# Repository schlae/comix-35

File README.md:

# COMIX-35 Home Computer
The COMIX-35 is an open-source clone of the 1980s COMX-35 8-bit home computer.
It uses the RCA 1802 microprocessor which is strange and slow but holds the
distinction of being the first CMOS microprocessor. The "35" is because the
original computer has 32K of main memory + 3K of video RAM.

There are a number of differences between the COMIX-35 and the original:

* Single +5V power supply
* Uses SRAM; no stolen cycles for DRAM refresh
* Configurable PAL or NTSC by changing three jumpers and swapping a crystal
* Additional CPU crystal for a new turbo mode
* Mechanical key switches for your typing comfort
* Cassette input data light indicates incoming information

## Design files

Here are the design files. The BOM includes Mouser part numbers for everything
except the CDP1802, CDP1869, CDP1870, CDP1871, the trimmer capacitor (optional),
and the expansion slot header (also optional). I recommend you purchase IC
sockets for the four CDP parts, as well as for the ROM chip U15.

[Schematic](https://github.com/schlae/comix-35/blob/master/COMIX-35.pdf)

[Bill of Materials](https://github.com/schlae/comix-35/blob/master/COMIX-35.csv)

[Fab Files](https://github.com/schlae/comix-35/blob/master/fab/COMIX-35.zip)

The board is rather large, at 12 x 6.5 inches (304.8 x 165.1 mm), but it does
include the keyboard. It is a 2-layer design so it should be relatively cheap
to manufacture. A word of advice: pick out your keycap set first, then choose
the PCB color to match it.

The keyboard keyswitches are easily substituted for lower-cost ones from other
vendors. I recommend you purchase DSA-profile keycaps since some of the keys
are located in rows that are not typical. I ended up buying the [YMDK 125 DSA Dye Sub 9009 Retro PBT Full Keyset for MX](https://www.amazon.com/gp/product/B083L6FVPN/). You can choose whatever you want, but make sure there is a 1 unit
control key and a 1.25 unit shift key. The enter key needs to be 1.5 unit, so
I just used the tab key for that instead. If you have any doubt, check the PCB
layout which has the key cap unit sizes marked below each key.

I have not included part numbers for the 0.1" headers which usually come as a
long strip that you break into the appropriately-sized sections.

Most other components may be safely substituted. U4 is a little tricky. It
should be a 74HCU04 in order for the oscillators to operate, but in a pinch,
a 74HC04 will also work. A 74LS04 or a part from another logic family will
not work.

## Assembly notes
Since the standard COMX-35 ROM configures the CDP1869 to use extra-tall
characters, you need to tie CDP1869 pin 25 to CMA3. Do this by soldering a
jumper wire from pin 1-2 on JP6. If you wish to write your own code to deal
with short characters and more text pages, then install a 0.1" header and
jumper instead.

The default configuration for PAL is as follows:

| Location | PAL     | NTSC    |
| -------- | ------- | ------- |
| JP1      | 2-3     | 1-2     |
| JP2      | 2-3     | 1-2     |
| JP3      | 2-3     | 1-2     |
| Y1       | 17.734 MHz | 14.318MHz |

The trimmer capacitor, C12, is optional. It allows you to adjust the color
image for best clarity. If you don't use it, then just stuff C13 with a 22pF
capacitor.

You can also configure your COMIX-35 for turbo mode which allows the CPU to
run at much higher frequencies than the original computer, limited only by
the maximum frequency of your particular CDP1802. Check the datasheet for the
variation you have, or experiment. Turbo mode is enabled by jumpering JP4 to
position 1-2. This enables the clock oscillator installed at Y3. To run at the
standard speed, set JP4 to 2-3.

If you use a 28C256 or 27C256 ROM, jumper JP5 will allow you to select between
the upper and lower 16K of ROM. This is useful if you want to use store two
different ROM binaries, such as the standard COMX-35 ROM and your own custom
program.

The COMX-35 ROM image is relatively easy to find so I will not provide it here.

## Video adjustments

There are two trimmer resistors that adjust the video:

* RV3 adjusts the sync pulse amplitude
* RV4 sets the overall video amplitude

The simplest way to get it working is to use an oscilloscope to set the sync
pulse amplitude to about 300mV and the video amplitude to about 700mV. If you
don't have an oscilloscope, set RV4 to the maximum, set RV3 to the minimum,
and then slowly increase RV3 until you get a stable picture. If the colors
are not saturated enough, you can decrease RV4.

The C12 trimmer capacitor, if you installed it, adjusts the frequency of the
colorburst by a small amount. Since the colorburst and the pixel clock are not
sychronized, you'll get a "shimmering" effect on colored pixels. Adjust C12
until you can't see shimmering anymore. 

## Loading programs off a computer using the cassette port
The process I've had success with is this:

* Run the [Emma 02 emulator](https://www.emma02.hobby-site.com/). Turn off SB
mode, turn off Turbo LOAD/SAVE. Make sure Auto LOAD/SAVE is turned on.
* Hit run. Press enter to go past the COMX screen and get to the BASIC prompt.
* Click the LOAD button and select the program you are interested in.
* From BASIC, type PSAVE.
* Name the file (it is actually a raw sound file, not WAV.)
* It will take a while but it will eventually save the cassette sound.
* Load the raw file in Audacity using File-\>Import-\>Raw Data. Select 22050 as
the sampling rate, mono, signed 16 bit little endian.
* You may wish to save the program as a regular WAV file at this point.
* Connect an audio cable between the COMIX-35's EAR jack and your computer's
speaker output.
* Make sure your computer has absolutely no audio processing going on at all.
No echo, no equalizer, nothing at all. You may have to really crank up the
volume.
* Hit play, and then adjust the input bias control until the data LED flickers.
* Stop, rewind, hit play, and then (on the COMIX-35) type "PLOAD" and hit
enter. If everything works, PLOAD will return you back to the BASIC prompt.
* Type RUN and hit enter to start the program.

The cassette interface is a bit tricky to work due to various reasons. The
input circuit uses a Schmitt-trigger buffer, so the DC bias of the incoming
audio signal must be adjusted to the halfway point of that threshold. This
is what the INPUT BIAS trimmer does.

You also need enough volume to be able to exceed the rising and falling
thresholds.

Tips and tricks if things don't work right the first time:
* Does your computer *really* provide clean audio? You've turned off all
effects processing? Audio managers, headphone bass boosters--all that *must* 
be turned off!
* Check your cables
* Check the volume level on the PC. If it is too low, it will not work
* Connect an oscilloscope to the cathode of D5 and make sure you see a clean
waveform

## Compatibility
Note that I have not tested the COMIX-35 with real COMX-35 accessories, such
as the expansion chassis, RAM boards, disk controllers, etc. It should work
with all these accessories except for the RAM expansion because it uses the RAS
and CAS lines. Since the COMIX-35 does not have the DRAM refresh circuit, these
signals don't exist on the expansion connector.

## License
This work is licensed under a Creative Commons Attribution-ShareAlike 4.0
International License. See [https://creativecommons.org/licenses/by-sa/4.0/](https://creativecommons.org/licenses/by-sa/4.0/).

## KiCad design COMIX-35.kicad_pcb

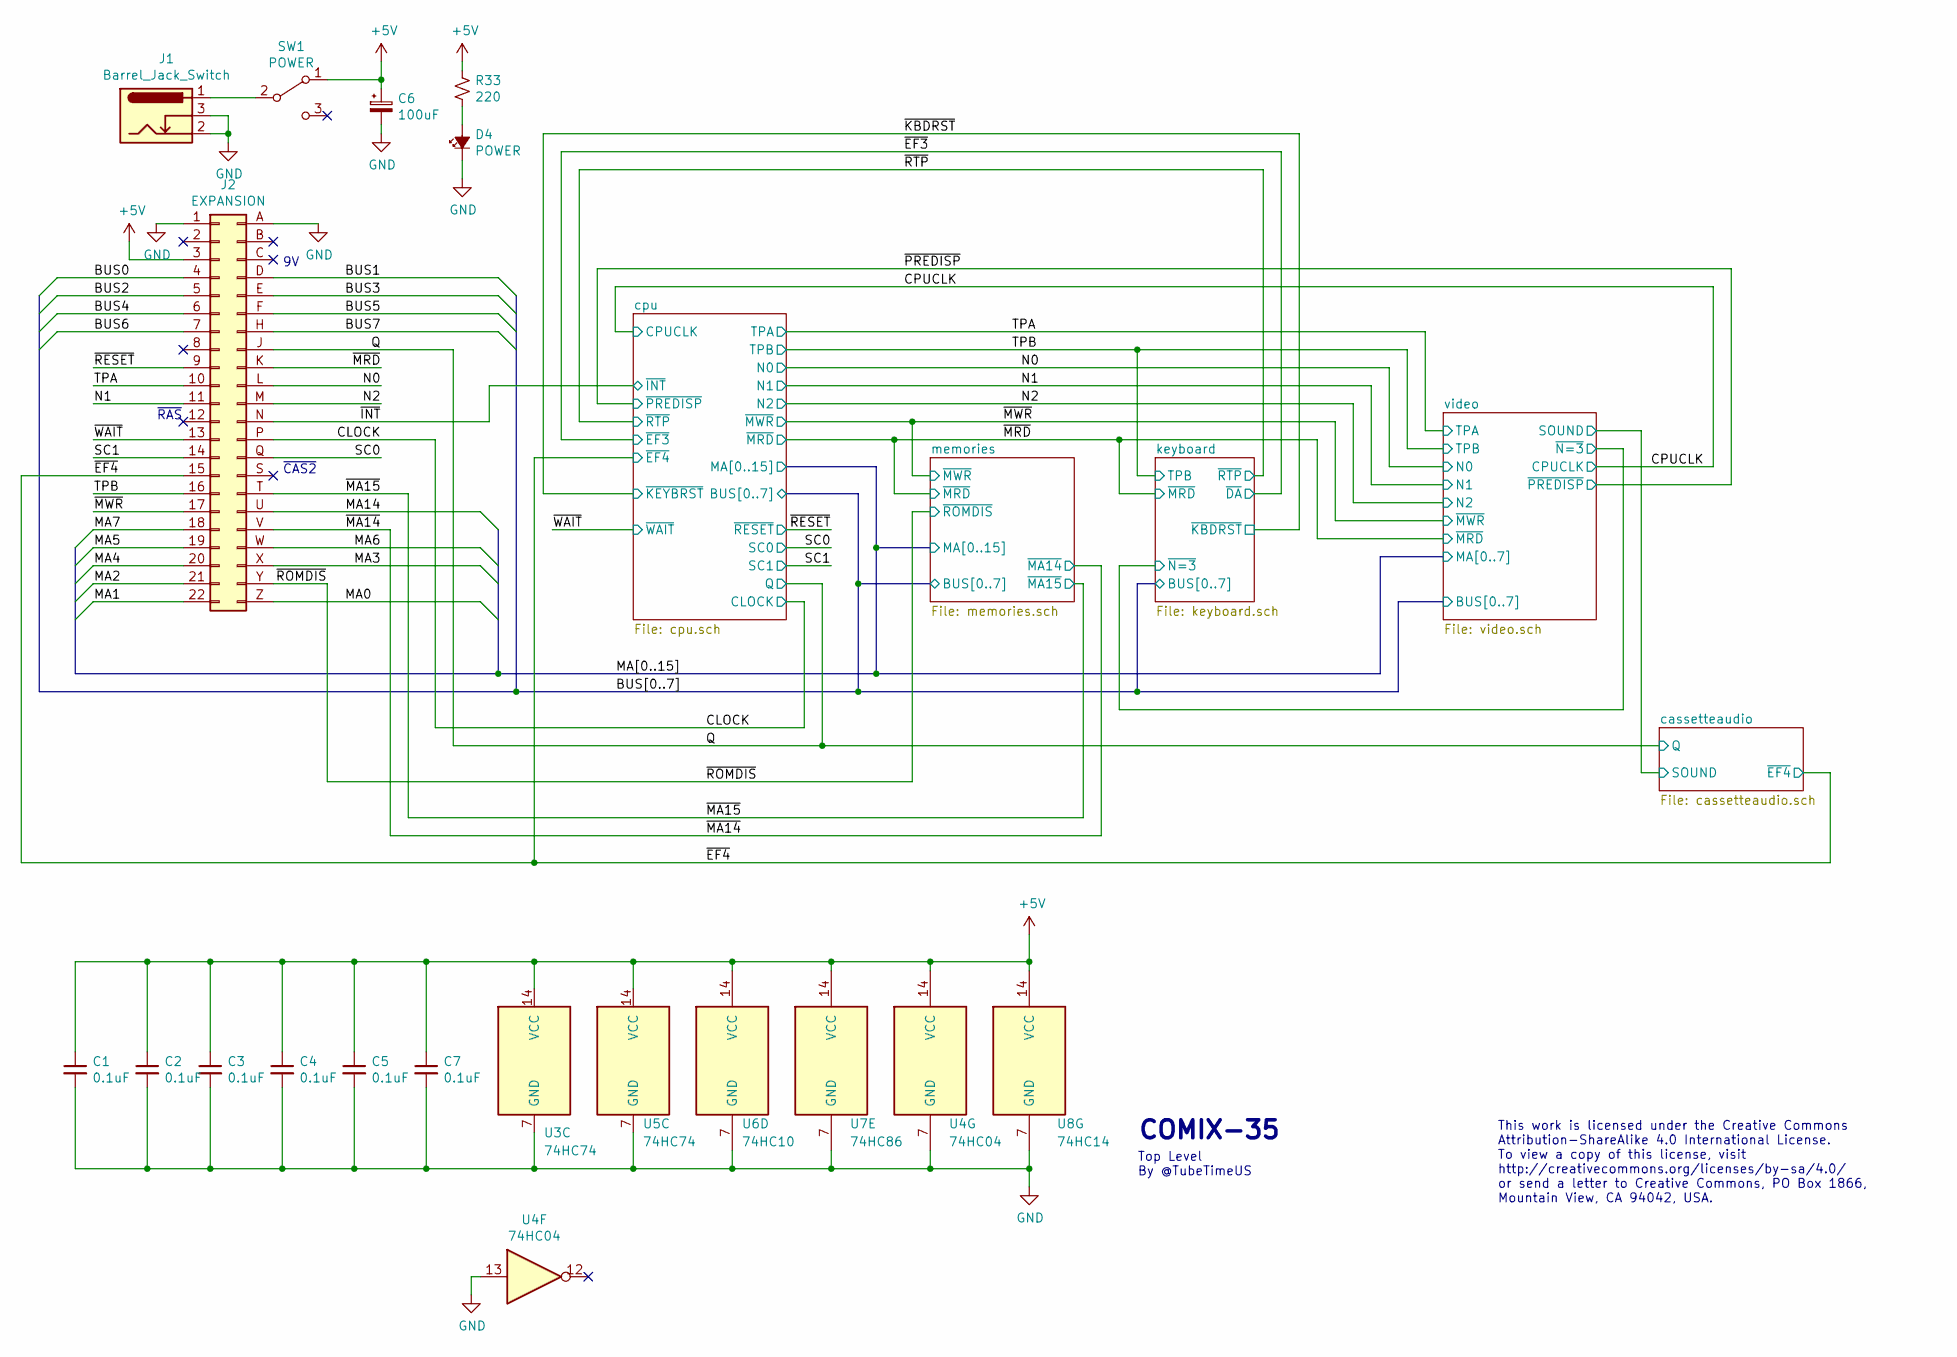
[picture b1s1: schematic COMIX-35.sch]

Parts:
C1, C2, C3, C4, C5, C7: 0.1uF; CAPAC200; Mouser 581-SA105E104M
C6: 100uF; CAPAE200P500X1100; Mouser 667-ECA-1CM101I
D4: POWER; LED_D5.0mm; Mouser 859-LTL-4213
J1: Barrel_Jack_Switch; CUI_PJ-002B; Mouser 490-PJ-002B
J2: EXPANSION; SULLINS_EBC22DRAS_ALT; Digikey S3316-ND
R33: 220; RESA500; Mouser 603-CFR-25JR-52220R
SW1: POWER; NKK_CS12ANW03; Mouser 633-CS12ANW03
U3, U5: 74HC74; DIP254P762X635-14; Mouser 595-SN74HC74N
U4: 74HC04; DIP254P762X635-14; Mouser 595-SN74HC04N
U6: 74HC10; DIP254P762X635-14; Mouser 595-SN74HC10N
U7: 74HC86; DIP254P762X635-14; Mouser 595-SN74HC86N
U8: 74HC14; DIP254P762X635-14; Mouser 595-SN74HC14N

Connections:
+5V: C1.1, C2.1, C3.1, C4.1, C5.1, C6.1, C7.1, J2.3, R33.2, SW1.1 (A), U3.14 (VCC), U4.14 (VCC), U5.14 (VCC), U6.14 (VCC), U7.14 (VCC), U8.14 (VCC); also elsewhere on the board
/BUS0: J2.4; also elsewhere on the board
/BUS1: J2.D; also elsewhere on the board
/BUS2: J2.5; also elsewhere on the board
/BUS3: J2.E; also elsewhere on the board
/BUS4: J2.6; also elsewhere on the board
/BUS5: J2.F; also elsewhere on the board
/BUS6: J2.7; also elsewhere on the board
/BUS7: J2.H; also elsewhere on the board
/CLOCK: J2.P; also elsewhere on the board
/MA0: J2.Z; also elsewhere on the board
/MA1: J2.22; also elsewhere on the board
/MA2: J2.21; also elsewhere on the board
/MA3: J2.X; also elsewhere on the board
/MA4: J2.20; also elsewhere on the board
/MA5: J2.19; also elsewhere on the board
/MA6: J2.W; also elsewhere on the board
/MA7: J2.18; also elsewhere on the board
/MA14: J2.U; also elsewhere on the board
/N0: J2.L; also elsewhere on the board
/N1: J2.11; also elsewhere on the board
/N2: J2.M; also elsewhere on the board
/Q: J2.J; also elsewhere on the board
/SC0: J2.Q; also elsewhere on the board
/SC1: J2.14; also elsewhere on the board
/TPA: J2.10; also elsewhere on the board
/TPB: J2.16; also elsewhere on the board
/~EF4: J2.15; also elsewhere on the board
/~INT: J2.N; also elsewhere on the board
/~MA14: J2.V; also elsewhere on the board
/~MA15: J2.T; also elsewhere on the board
/~MRD: J2.K; also elsewhere on the board
/~MWR: J2.17; also elsewhere on the board
/~RESET: J2.9; also elsewhere on the board
/~ROMDIS: J2.Y; also elsewhere on the board
/~WAIT: J2.13; also elsewhere on the board
GND: C1.2, C2.2, C3.2, C4.2, C5.2, C6.2, C7.2, D4.1 (K), J1.2, J1.3, J2.1, J2.A, U3.7 (GND), U4.7 (GND), U4.13, U5.7 (GND), U6.7 (GND), U7.7 (GND), U8.7 (GND); also elsewhere on the board
unnamed: D4.2 (A), R33.1
unnamed: J1.1, SW1.2 (B)

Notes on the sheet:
~RAS
~CAS2
This work is licensed under the Creative Commons Attribution-ShareAlike 4.0 International License. To view a copy of this license, visit http://creativecommons.org/licenses/by-sa/4.0/ or send a letter to Creative Commons, PO Box 1866, Mountain View, CA 94042, USA.
COMIX-35
Top Level By @TubeTimeUS

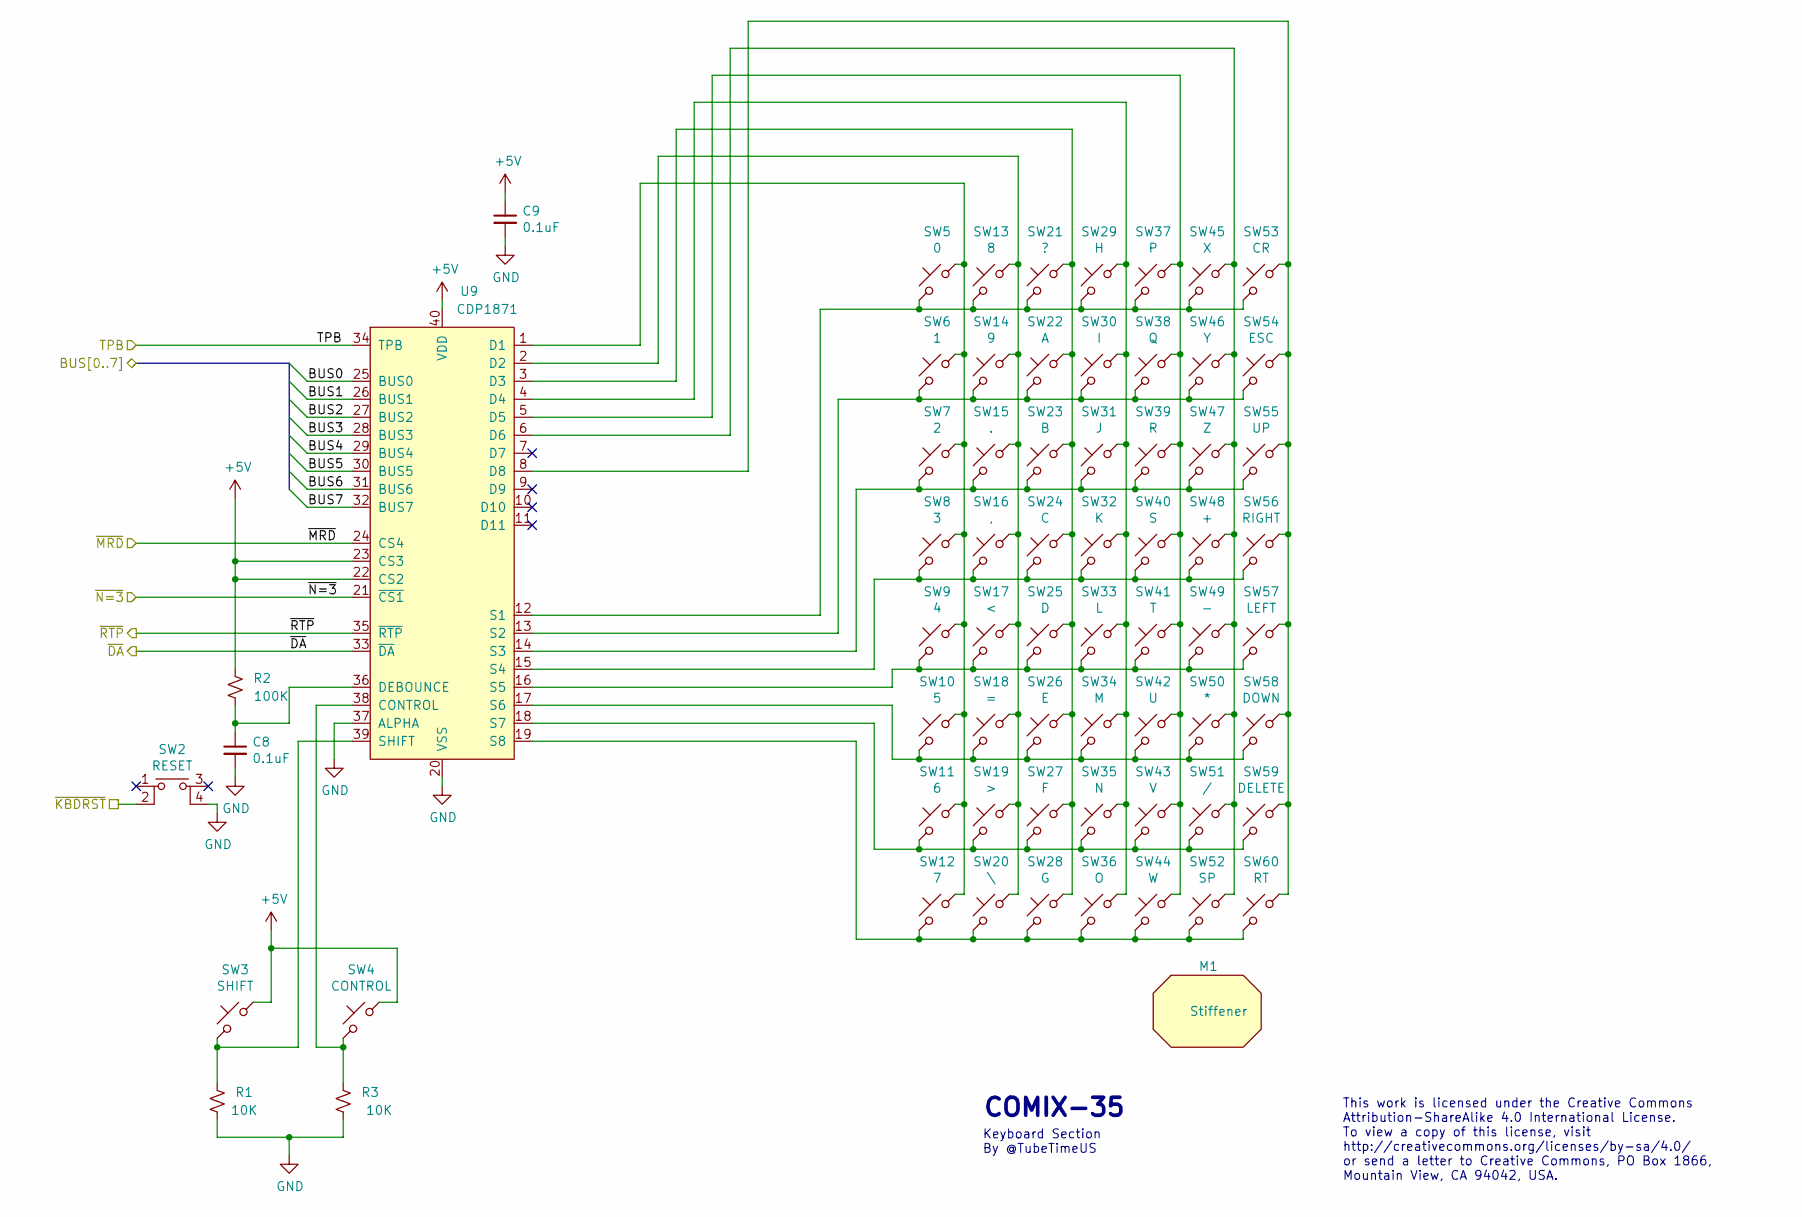
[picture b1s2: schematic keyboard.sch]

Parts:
C8, C9: 0.1uF; CAPAC200; Mouser 581-SA105E104M
M1: Stiffener; CHERRY_ST2; Mouser 540-0G990743
R1, R3: 10K; RESA500; Mouser 603-CFR-25JB-52-10K
R2: 100K; RESA500; Mouser 603-CFR-25JB-52-100K
SW2: RESET; ESWITCH_TL1105; Mouser 612-TL1105B
SW3: SHIFT; CHERRY_MX_125; Mouser 540-MX1A-11NW
SW4: CONTROL; CHERRY_MX; Mouser 540-MX1A-11NW
SW5: 0; CHERRY_MX; Mouser 540-MX1A-11NW
SW6: 1; CHERRY_MX; Mouser 540-MX1A-11NW
SW7: 2; CHERRY_MX; Mouser 540-MX1A-11NW
SW8: 3; CHERRY_MX; Mouser 540-MX1A-11NW
SW9: 4; CHERRY_MX; Mouser 540-MX1A-11NW
SW10: 5; CHERRY_MX; Mouser 540-MX1A-11NW
SW11: 6; CHERRY_MX; Mouser 540-MX1A-11NW
SW12: 7; CHERRY_MX; Mouser 540-MX1A-11NW
SW13: 8; CHERRY_MX; Mouser 540-MX1A-11NW
SW14: 9; CHERRY_MX; Mouser 540-MX1A-11NW
SW15: .; CHERRY_MX; Mouser 540-MX1A-11NW
SW16: ,; CHERRY_MX; Mouser 540-MX1A-11NW
SW17: <; CHERRY_MX; Mouser 540-MX1A-11NW
SW18: =; CHERRY_MX; Mouser 540-MX1A-11NW
SW19: >; CHERRY_MX; Mouser 540-MX1A-11NW
SW20: \\; CHERRY_MX; Mouser 540-MX1A-11NW
SW21: ?; CHERRY_MX; Mouser 540-MX1A-11NW
SW22: A; CHERRY_MX; Mouser 540-MX1A-11NW
SW23: B; CHERRY_MX; Mouser 540-MX1A-11NW
SW24: C; CHERRY_MX; Mouser 540-MX1A-11NW
SW25: D; CHERRY_MX; Mouser 540-MX1A-11NW
SW26: E; CHERRY_MX; Mouser 540-MX1A-11NW
SW27: F; CHERRY_MX; Mouser 540-MX1A-11NW
SW28: G; CHERRY_MX; Mouser 540-MX1A-11NW
SW29: H; CHERRY_MX; Mouser 540-MX1A-11NW
SW30: I; CHERRY_MX; Mouser 540-MX1A-11NW
SW31: J; CHERRY_MX; Mouser 540-MX1A-11NW
SW32: K; CHERRY_MX; Mouser 540-MX1A-11NW
SW33: L; CHERRY_MX; Mouser 540-MX1A-11NW
SW34: M; CHERRY_MX; Mouser 540-MX1A-11NW
SW35: N; CHERRY_MX; Mouser 540-MX1A-11NW
SW36: O; CHERRY_MX; Mouser 540-MX1A-11NW
SW37: P; CHERRY_MX; Mouser 540-MX1A-11NW
SW38: Q; CHERRY_MX; Mouser 540-MX1A-11NW
SW39: R; CHERRY_MX; Mouser 540-MX1A-11NW
SW40: S; CHERRY_MX; Mouser 540-MX1A-11NW
SW41: T; CHERRY_MX; Mouser 540-MX1A-11NW
SW42: U; CHERRY_MX; Mouser 540-MX1A-11NW
SW43: V; CHERRY_MX; Mouser 540-MX1A-11NW
SW44: W; CHERRY_MX; Mouser 540-MX1A-11NW
SW45: X; CHERRY_MX; Mouser 540-MX1A-11NW
SW46: Y; CHERRY_MX; Mouser 540-MX1A-11NW
SW47: Z; CHERRY_MX; Mouser 540-MX1A-11NW
SW48: +; CHERRY_MX; Mouser 540-MX1A-11NW
SW49: -; CHERRY_MX; Mouser 540-MX1A-11NW
SW50: *; CHERRY_MX; Mouser 540-MX1A-11NW
SW51: /; CHERRY_MX; Mouser 540-MX1A-11NW
SW52: SP; CHERRY_MX_625; Mouser 540-MX1A-11NW
SW53: CR; CHERRY_MX_150; Mouser 540-MX1A-11NW
SW54: ESC; CHERRY_MX; Mouser 540-MX1A-11NW
SW55: UP; CHERRY_MX; Mouser 540-MX1A-11NW
SW56: RIGHT; CHERRY_MX; Mouser 540-MX1A-11NW
SW57: LEFT; CHERRY_MX; Mouser 540-MX1A-11NW
SW58: DOWN; CHERRY_MX; Mouser 540-MX1A-11NW
SW59: DELETE; CHERRY_MX; Mouser 540-MX1A-11NW
SW60: RT; CHERRY_MX; Mouser 540-MX1A-11NW
U9: CDP1871; DIP254P1524X635-40

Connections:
+5V: C9.1, R2.1, SW3.1, SW4.1, U9.22 (CS2), U9.23 (CS3), U9.40 (VDD); also elsewhere on the board
/BUS0: U9.25 (BUS0); also elsewhere on the board
/BUS1: U9.26 (BUS1); also elsewhere on the board
/BUS2: U9.27 (BUS2); also elsewhere on the board
/BUS3: U9.28 (BUS3); also elsewhere on the board
/BUS4: U9.29 (BUS4); also elsewhere on the board
/BUS5: U9.30 (BUS5); also elsewhere on the board
/BUS6: U9.31 (BUS6); also elsewhere on the board
/BUS7: U9.32 (BUS7); also elsewhere on the board
/TPB: U9.34 (TPB); also elsewhere on the board
/keyboard/~N=3: U9.21 (~CS1); also elsewhere on the board
/~EF3: U9.33 (~DA); also elsewhere on the board
/~KBDRST: SW2.2; also elsewhere on the board
/~MRD: U9.24 (CS4); also elsewhere on the board
/~RTP: U9.35 (~RTP); also elsewhere on the board
GND: C8.2, C9.2, R1.2, R3.2, SW2.4, U9.20 (VSS), U9.37 (ALPHA); also elsewhere on the board
unnamed: C8.1, R2.2, U9.36 (DEBOUNCE)
unnamed: R1.1, SW3.2, U9.39 (SHIFT)
unnamed: R3.1, SW4.2, U9.38 (CONTROL)
unnamed: SW5.1, SW6.1, SW7.1, SW8.1, SW9.1, SW10.1, SW11.1, SW12.1, U9.1 (D1)
unnamed: SW10.2, SW18.2, SW26.2, SW34.2, SW42.2, SW50.2, SW58.2, U9.17 (S6)
unnamed: SW11.2, SW19.2, SW27.2, SW35.2, SW43.2, SW51.2, SW59.2, U9.18 (S7)
unnamed: SW12.2, SW20.2, SW28.2, SW36.2, SW44.2, SW52.2, SW60.2, U9.19 (S8)
unnamed: SW13.1, SW14.1, SW15.1, SW16.1, SW17.1, SW18.1, SW19.1, SW20.1, U9.2 (D2)
unnamed: SW5.2, SW13.2, SW21.2, SW29.2, SW37.2, SW45.2, SW53.2, U9.12 (S1)
unnamed: SW6.2, SW14.2, SW22.2, SW30.2, SW38.2, SW46.2, SW54.2, U9.13 (S2)
unnamed: SW7.2, SW15.2, SW23.2, SW31.2, SW39.2, SW47.2, SW55.2, U9.14 (S3)
unnamed: SW8.2, SW16.2, SW24.2, SW32.2, SW40.2, SW48.2, SW56.2, U9.15 (S4)
unnamed: SW9.2, SW17.2, SW25.2, SW33.2, SW41.2, SW49.2, SW57.2, U9.16 (S5)
unnamed: SW21.1, SW22.1, SW23.1, SW24.1, SW25.1, SW26.1, SW27.1, SW28.1, U9.3 (D3)
unnamed: SW29.1, SW30.1, SW31.1, SW32.1, SW33.1, SW34.1, SW35.1, SW36.1, U9.4 (D4)
unnamed: SW37.1, SW38.1, SW39.1, SW40.1, SW41.1, SW42.1, SW43.1, SW44.1, U9.5 (D5)
unnamed: SW45.1, SW46.1, SW47.1, SW48.1, SW49.1, SW50.1, SW51.1, SW52.1, U9.6 (D6)
unnamed: SW53.1, SW54.1, SW55.1, SW56.1, SW57.1, SW58.1, SW59.1, SW60.1, U9.8 (D8)

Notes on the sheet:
This work is licensed under the Creative Commons Attribution-ShareAlike 4.0 International License. To view a copy of this license, visit http://creativecommons.org/licenses/by-sa/4.0/ or send a letter to Creative Commons, PO Box 1866, Mountain View, CA 94042, USA.
COMIX-35
Keyboard Section By @TubeTimeUS

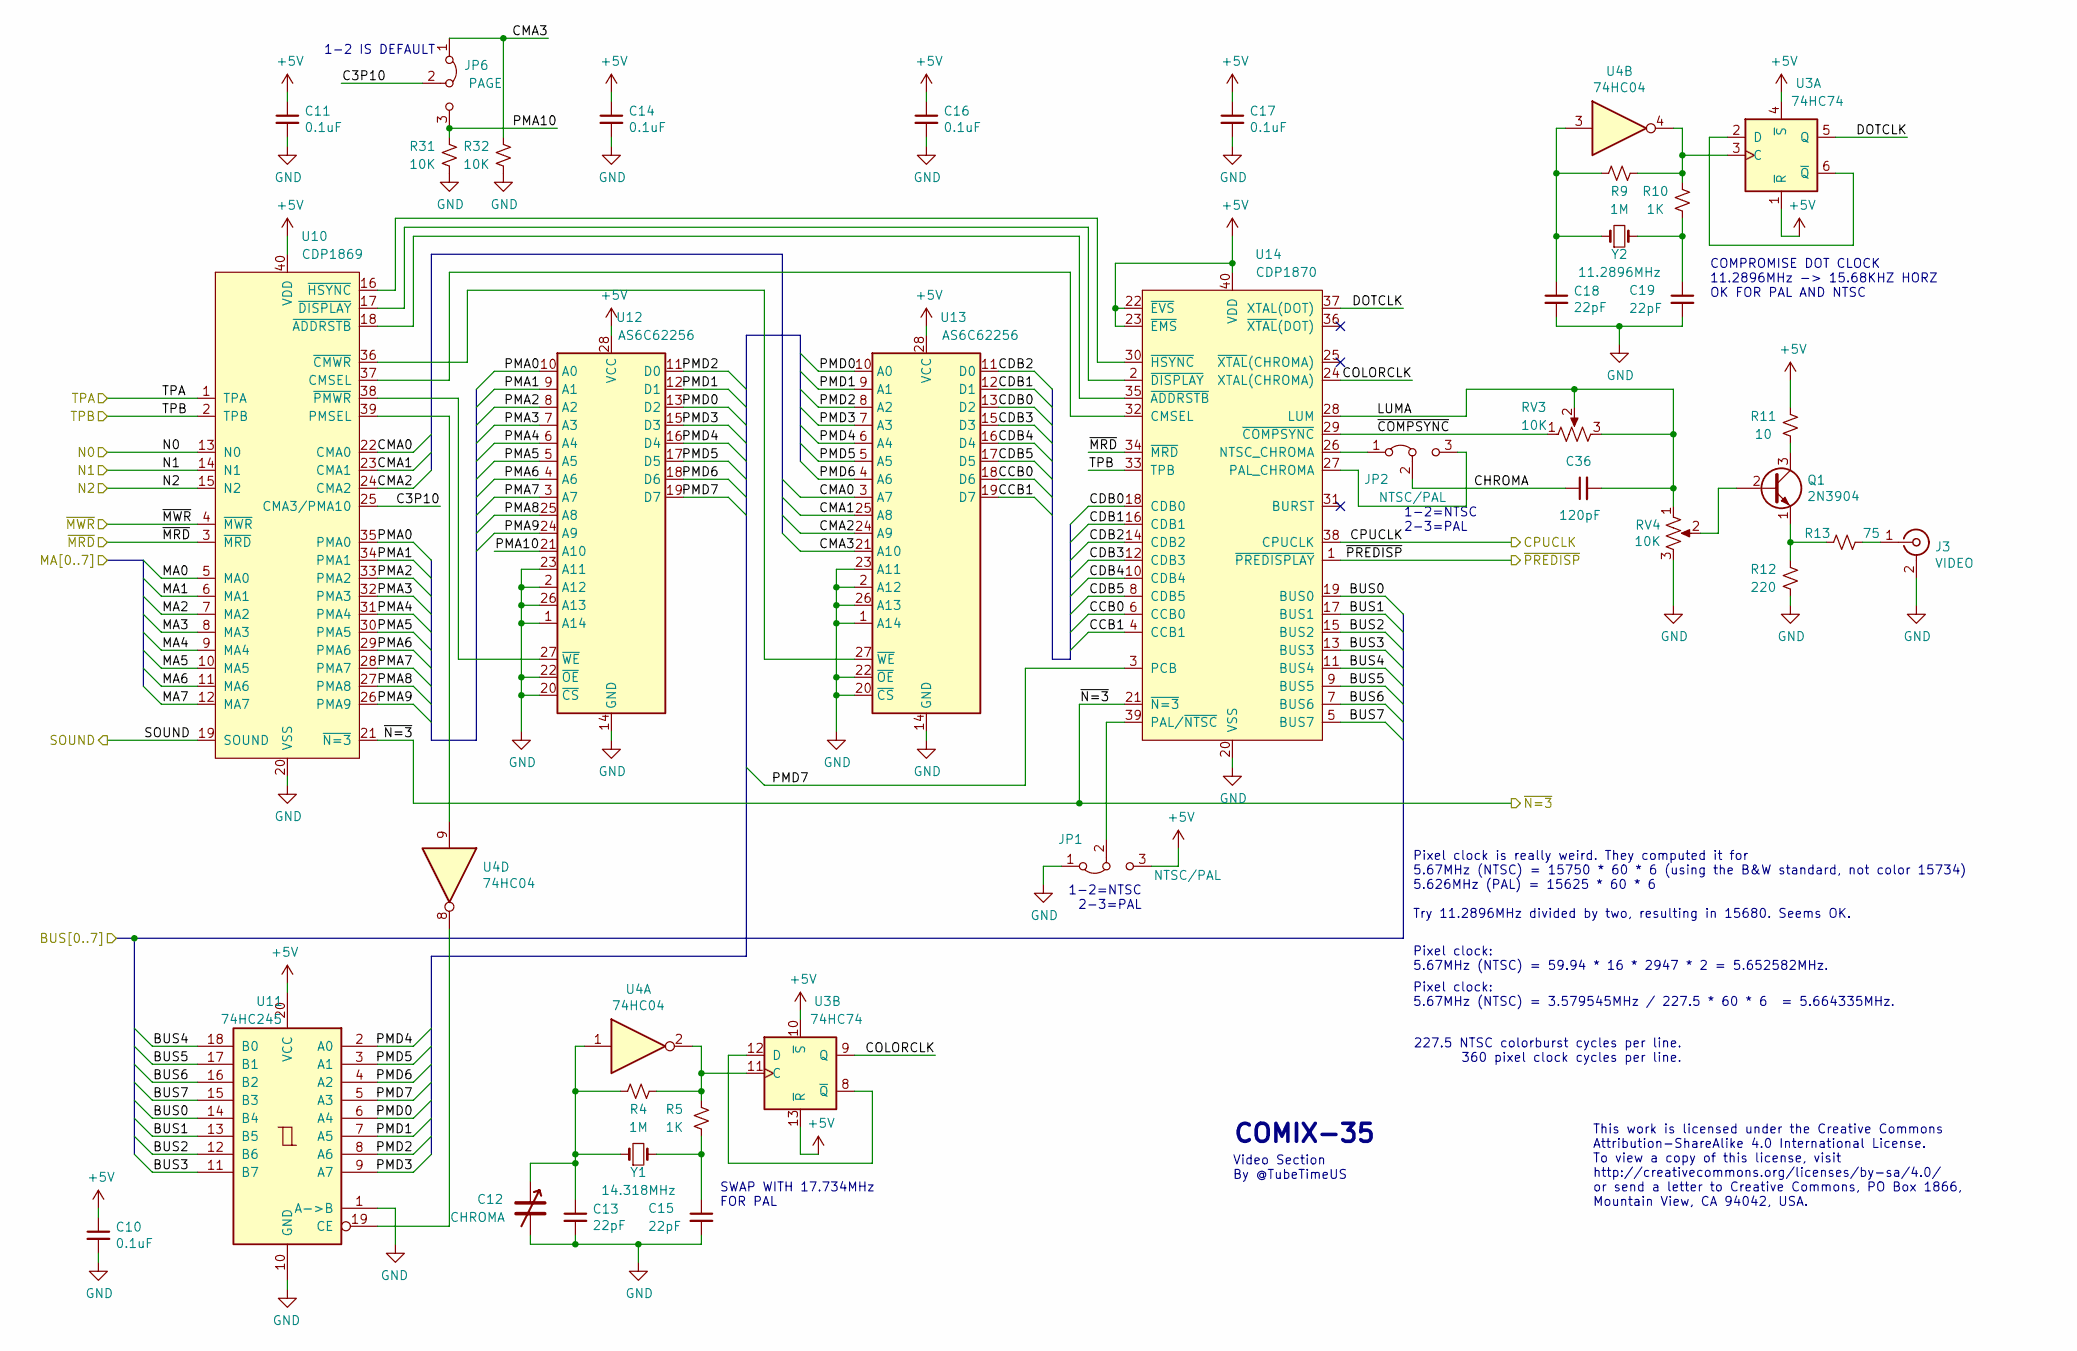
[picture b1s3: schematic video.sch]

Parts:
C10, C11, C14, C16, C17: 0.1uF; CAPAC200; Mouser 581-SA105E104M
C12: CHROMA; EW_GKG; Digikey 2447-GKG30015-ND
C13, C15, C18, C19: 22pF; CAPAC200; Mouser 810-FG28C0G2A220JNT0
C36: 120pF; CAPAC200; Mouser 810-FG28C0G1H121JNT6
J3: VIDEO; KOBICONN_161-03X0-E; Mouser 161-0360-E
JP1, JP2: NTSC/PAL; Pin_Header_Straight_1x03_Pitch2.54mm
JP6: PAGE; Pin_Header_Straight_1x03_Pitch2.54mm
Q1: 2N3904; TO92-IL; Mouser 512-2N3904BU
R4, R9: 1M; RESA500; Mouser 603-CFR-25JR-521M
R5, R10: 1K; RESA500; Mouser 603-CFR-25JR-521K
R11: 10; RESA500; Mouser 603-CFR-25JR-5210R
R12: 220; RESA500; Mouser 603-CFR-25JR-52220R
R13: 75; RESA500; Mouser 603-CFR-25JR-5275R
R31, R32: 10K; RESA500; Mouser 603-CFR-25JB-52-10K
RV3, RV4: 10K; PIHER_PT10_H01; Mouser 531-PT10H-10K-S
U3: 74HC74; DIP254P762X635-14; Mouser 595-SN74HC74N
U4: 74HC04; DIP254P762X635-14; Mouser 595-SN74HC04N
U10: CDP1869; DIP254P1524X635-40
U11: 74HC245; DIP254P762X635-20; Mouser 595-SN74HC245N
U12, U13: AS6C62256; DIP254P1524X635-28; Mouser 913-AS6C62256-55PCN
U14: CDP1870; DIP254P1524X635-40
Y1: 14.318MHz; Crystal_HC49-4H_Vertical; Mouser 815-ABL-14.31818B2
Y2: 11.2896MHz; Crystal_HC49-4H_Vertical; Mouser 815-ABL-11.2896-B4Y

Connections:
+5V: C10.1, C11.1, C14.1, C16.1, C17.1, JP1.3 (B), R11.1, U3.1 (~R), U3.4 (~S), U3.10 (~S), U3.13 (~R), U10.40 (VDD), U11.20 (VCC), U12.28 (VCC), U13.28 (VCC), U14.22 (~EVS), U14.23 (~EMS), U14.40 (VDD); also elsewhere on the board
/BUS0: U11.14 (B4), U14.19 (BUS0); also elsewhere on the board
/BUS1: U11.13 (B5), U14.17 (BUS1); also elsewhere on the board
/BUS2: U11.12 (B6), U14.15 (BUS2); also elsewhere on the board
/BUS3: U11.11 (B7), U14.13 (BUS3); also elsewhere on the board
/BUS4: U11.18 (B0), U14.11 (BUS4); also elsewhere on the board
/BUS5: U11.17 (B1), U14.9 (BUS5); also elsewhere on the board
/BUS6: U11.16 (B2), U14.7 (BUS6); also elsewhere on the board
/BUS7: U11.15 (B3), U14.5 (BUS7); also elsewhere on the board
/CPUCLK: U14.38 (CPUCLK); also elsewhere on the board
/MA0: U10.5 (MA0); also elsewhere on the board
/MA1: U10.6 (MA1); also elsewhere on the board
/MA2: U10.7 (MA2); also elsewhere on the board
/MA3: U10.8 (MA3); also elsewhere on the board
/MA4: U10.9 (MA4); also elsewhere on the board
/MA5: U10.10 (MA5); also elsewhere on the board
/MA6: U10.11 (MA6); also elsewhere on the board
/MA7: U10.12 (MA7); also elsewhere on the board
/N0: U10.13 (N0); also elsewhere on the board
/N1: U10.14 (N1); also elsewhere on the board
/N2: U10.15 (N2); also elsewhere on the board
/TPA: U10.1 (TPA); also elsewhere on the board
/TPB: U10.2 (TPB), U14.33 (TPB); also elsewhere on the board
/cassetteaudio/SOUND: U10.19 (SOUND); also elsewhere on the board
/keyboard/~N=3: U10.21 (~N=3), U14.21 (~N=3); also elsewhere on the board
/video/C3P10: JP6.2 (C), U10.25 (CMA3/PMA10)
/video/CCB0: U13.18 (D6), U14.6 (CCB0)
/video/CCB1: U13.19 (D7), U14.4 (CCB1)
/video/CDB0: U13.13 (D2), U14.18 (CDB0)
/video/CDB1: U13.12 (D1), U14.16 (CDB1)
/video/CDB2: U13.11 (D0), U14.14 (CDB2)
/video/CDB3: U13.15 (D3), U14.12 (CDB3)
/video/CDB4: U13.16 (D4), U14.10 (CDB4)
/video/CDB5: U13.17 (D5), U14.8 (CDB5)
/video/CHROMA: C36.1, JP2.2 (C)
/video/CMA0: U10.22 (CMA0), U13.3 (A7)
/video/CMA1: U10.23 (CMA1), U13.25 (A8)
/video/CMA2: U10.24 (CMA2), U13.24 (A9)
/video/CMA3: JP6.1 (A), R32.1, U13.21 (A10)
/video/COLORCLK: U3.9 (Q), U14.24 (XTAL(CHROMA))
/video/DOTCLK: U3.5 (Q), U14.37 (XTAL(DOT))
/video/LUMA: C36.2, RV3.2, RV3.3, RV4.1, U14.28 (LUM)
/video/PMA0: U10.35 (PMA0), U12.10 (A0)
/video/PMA1: U10.34 (PMA1), U12.9 (A1)
/video/PMA2: U10.33 (PMA2), U12.8 (A2)
/video/PMA3: U10.32 (PMA3), U12.7 (A3)
/video/PMA4: U10.31 (PMA4), U12.6 (A4)
/video/PMA5: U10.30 (PMA5), U12.5 (A5)
/video/PMA6: U10.29 (PMA6), U12.4 (A6)
/video/PMA7: U10.28 (PMA7), U12.3 (A7)
/video/PMA8: U10.27 (PMA8), U12.25 (A8)
/video/PMA9: U10.26 (PMA9), U12.24 (A9)
/video/PMA10: JP6.3 (B), R31.1, U12.21 (A10)
/video/PMD0: U11.6 (A4), U12.13 (D2), U13.10 (A0)
/video/PMD1: U11.7 (A5), U12.12 (D1), U13.9 (A1)
/video/PMD2: U11.8 (A6), U12.11 (D0), U13.8 (A2)
/video/PMD3: U11.9 (A7), U12.15 (D3), U13.7 (A3)
/video/PMD4: U11.2 (A0), U12.16 (D4), U13.6 (A4)
/video/PMD5: U11.3 (A1), U12.17 (D5), U13.5 (A5)
/video/PMD6: U11.4 (A2), U12.18 (D6), U13.4 (A6)
/video/PMD7: U11.5 (A3), U12.19 (D7), U14.3 (PCB)
/video/~COMPSYNC: RV3.1, U14.29 (~COMPSYNC)
/~MRD: U10.3 (~MRD), U14.34 (~MRD); also elsewhere on the board
/~MWR: U10.4 (~MWR); also elsewhere on the board
/~PREDISP: U14.1 (~PREDISPLAY); also elsewhere on the board
GND: C10.2, C11.2, C12.2, C13.2, C14.2, C15.2, C16.2, C17.2, C18.2, C19.2, J3.2 (Ext), JP1.1 (A), R12.2, R31.2, R32.2, RV4.3, U10.20 (VSS), U11.1 (A->B), U11.10 (GND), U12.1 (A14), U12.2 (A12), U12.14 (GND), U12.20 (~CS), U12.22 (~OE), U12.23 (A11), U12.26 (A13), U13.1 (A14), U13.2 (A12), U13.14 (GND), U13.20 (~CS), U13.22 (~OE), U13.23 (A11), U13.26 (A13), U14.20 (VSS); also elsewhere on the board
unnamed: C12.1, C13.1, R4.1, U4.1, Y1.1
unnamed: C15.1, R5.2, Y1.2
unnamed: C18.1, R9.1, U4.3, Y2.1
unnamed: C19.1, R10.2, Y2.2
unnamed: J3.1 (In), R13.2
unnamed: JP1.2 (C), U14.39 (PAL/~NTSC)
unnamed: JP2.1 (A), U14.26 (NTSC_CHROMA)
unnamed: JP2.3 (B), U14.27 (PAL_CHROMA)
unnamed: Q1.1 (E), R12.1, R13.1
unnamed: Q1.2 (B), RV4.2
unnamed: Q1.3 (C), R11.2
unnamed: R4.2, R5.1, U3.11 (C), U4.2
unnamed: R9.2, R10.1, U3.3 (C), U4.4
unnamed: U3.2 (D), U3.6 (~Q)
unnamed: U3.8 (~Q), U3.12 (D)
unnamed: U10.16 (~HSYNC), U14.30 (~HSYNC)
unnamed: U10.17 (~DISPLAY), U14.2 (~DISPLAY)
unnamed: U10.18 (~ADDRSTB), U14.35 (~ADDRSTB)
unnamed: U10.36 (~CMWR), U13.27 (~WE)
unnamed: U10.37 (CMSEL), U14.32 (CMSEL)
unnamed: U10.38 (~PMWR), U12.27 (~WE)
unnamed: U4.9, U10.39 (PMSEL)
unnamed: U4.8, U11.19 (CE)

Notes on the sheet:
COMPROMISE DOT CLOCK 11.2896MHz -> 15.68KHZ HORZ OK FOR PAL AND NTSC
SWAP WITH 17.734MHz FOR PAL
1-2=NTSC 2-3=PAL
Pixel clock is really weird. They computed it for 5.67MHz (NTSC) = 15750 * 60 * 6 (using the B&W standard, not color 15734) 5.626MHz (PAL) = 15625 * 60 * 6 Try 11.2896MHz divided by two, resulting in 15680. Seems OK.
Pixel clock: 5.67MHz (NTSC) = 59.94 * 16 * 2947 * 2 = 5.652582MHz.
Pixel clock: 5.67MHz (NTSC) = 3.579545MHz / 227.5 * 60 * 6 = 5.664335MHz.
227.5 NTSC colorburst cycles per line. 360 pixel clock cycles per line.
1-2 IS DEFAULT
This work is licensed under the Creative Commons Attribution-ShareAlike 4.0 International License. To view a copy of this license, visit http://creativecommons.org/licenses/by-sa/4.0/ or send a letter to Creative Commons, PO Box 1866, Mountain View, CA 94042, USA.
COMIX-35
Video Section By @TubeTimeUS

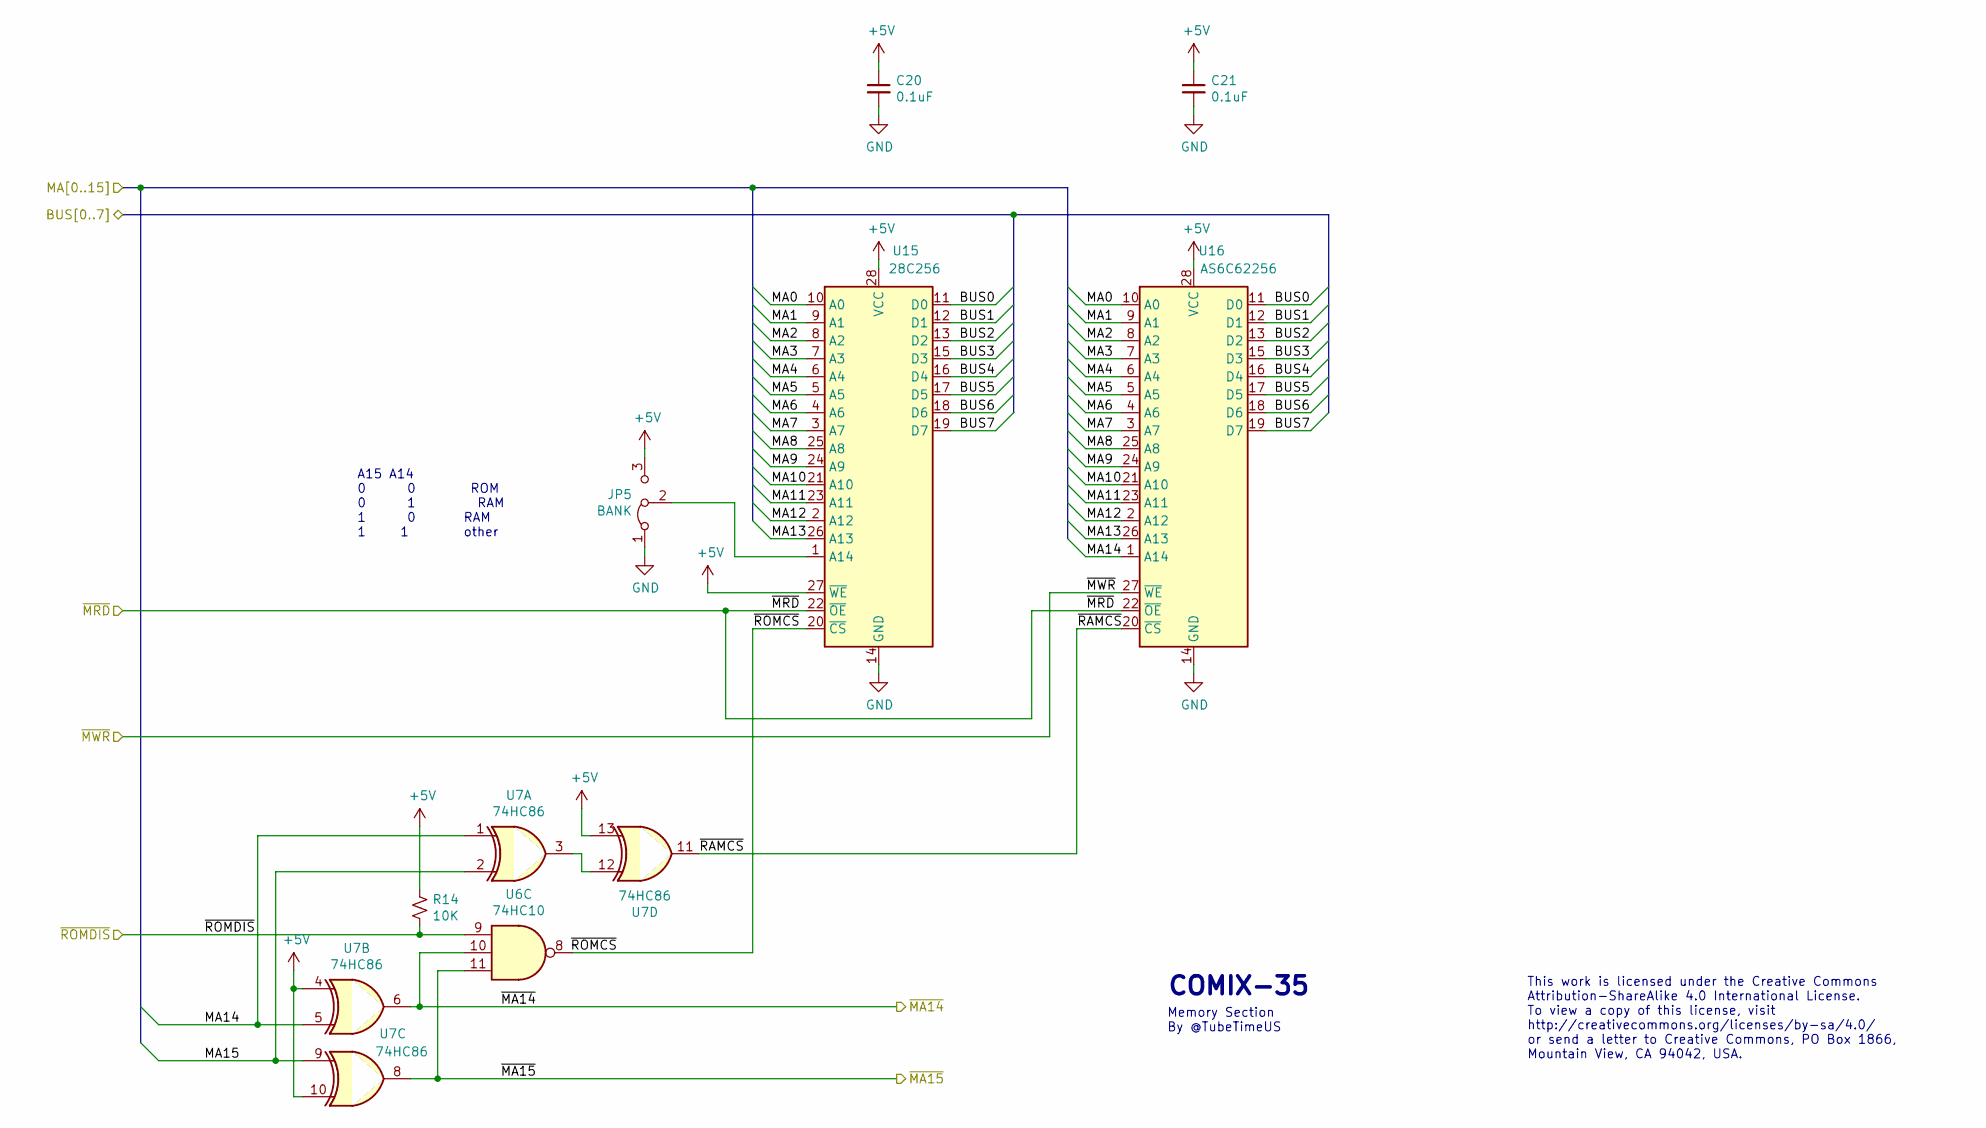
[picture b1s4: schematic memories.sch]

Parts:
C20, C21: 0.1uF; CAPAC200; Mouser 581-SA105E104M
JP5: BANK; Pin_Header_Straight_1x03_Pitch2.54mm
R14: 10K; RESA500; Mouser 603-CFR-25JB-52-10K
U6: 74HC10; DIP254P762X635-14; Mouser 595-SN74HC10N
U7: 74HC86; DIP254P762X635-14; Mouser 595-SN74HC86N
U15: 28C256; DIP254P1524X635-28; Mouser 556-AT28C25615PU
U16: AS6C62256; DIP254P1524X635-28; Mouser 913-AS6C62256-55PCN

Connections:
+5V: C20.1, C21.1, JP5.3 (B), R14.2, U7.4, U7.10, U7.13, U15.27 (~WE), U15.28 (VCC), U16.28 (VCC); also elsewhere on the board
/BUS0: U15.11 (D0), U16.11 (D0); also elsewhere on the board
/BUS1: U15.12 (D1), U16.12 (D1); also elsewhere on the board
/BUS2: U15.13 (D2), U16.13 (D2); also elsewhere on the board
/BUS3: U15.15 (D3), U16.15 (D3); also elsewhere on the board
/BUS4: U15.16 (D4), U16.16 (D4); also elsewhere on the board
/BUS5: U15.17 (D5), U16.17 (D5); also elsewhere on the board
/BUS6: U15.18 (D6), U16.18 (D6); also elsewhere on the board
/BUS7: U15.19 (D7), U16.19 (D7); also elsewhere on the board
/MA0: U15.10 (A0), U16.10 (A0); also elsewhere on the board
/MA1: U15.9 (A1), U16.9 (A1); also elsewhere on the board
/MA2: U15.8 (A2), U16.8 (A2); also elsewhere on the board
/MA3: U15.7 (A3), U16.7 (A3); also elsewhere on the board
/MA4: U15.6 (A4), U16.6 (A4); also elsewhere on the board
/MA5: U15.5 (A5), U16.5 (A5); also elsewhere on the board
/MA6: U15.4 (A6), U16.4 (A6); also elsewhere on the board
/MA7: U15.3 (A7), U16.3 (A7); also elsewhere on the board
/MA14: U7.1, U7.5, U16.1 (A14); also elsewhere on the board
/cpu/MA8: U15.25 (A8), U16.25 (A8); also elsewhere on the board
/cpu/MA9: U15.24 (A9), U16.24 (A9); also elsewhere on the board
/cpu/MA10: U15.21 (A10), U16.21 (A10); also elsewhere on the board
/cpu/MA11: U15.23 (A11), U16.23 (A11); also elsewhere on the board
/cpu/MA12: U15.2 (A12), U16.2 (A12); also elsewhere on the board
/cpu/MA13: U15.26 (A13), U16.26 (A13); also elsewhere on the board
/cpu/MA15: U7.2, U7.9; also elsewhere on the board
/memories/~RAMCS: U7.11, U16.20 (~CS)
/memories/~ROMCS: U6.8, U15.20 (~CS)
/~MA14: U6.10, U7.6; also elsewhere on the board
/~MA15: U6.11, U7.8; also elsewhere on the board
/~MRD: U15.22 (~OE), U16.22 (~OE); also elsewhere on the board
/~MWR: U16.27 (~WE); also elsewhere on the board
/~ROMDIS: R14.1, U6.9; also elsewhere on the board
GND: C20.2, C21.2, JP5.1 (A), U15.14 (GND), U16.14 (GND); also elsewhere on the board
unnamed: JP5.2 (C), U15.1 (A14)
unnamed: U7.3, U7.12

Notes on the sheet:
A15 A14 0 0 ROM 0 1 RAM 1 0 RAM 1 1 other
This work is licensed under the Creative Commons Attribution-ShareAlike 4.0 International License. To view a copy of this license, visit http://creativecommons.org/licenses/by-sa/4.0/ or send a letter to Creative Commons, PO Box 1866, Mountain View, CA 94042, USA.
COMIX-35
Memory Section By @TubeTimeUS

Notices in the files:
COMIX-35.kicad_pcb:
Copyright (C) 2020 Eric Schlaepfer
©2020 Tube Time
